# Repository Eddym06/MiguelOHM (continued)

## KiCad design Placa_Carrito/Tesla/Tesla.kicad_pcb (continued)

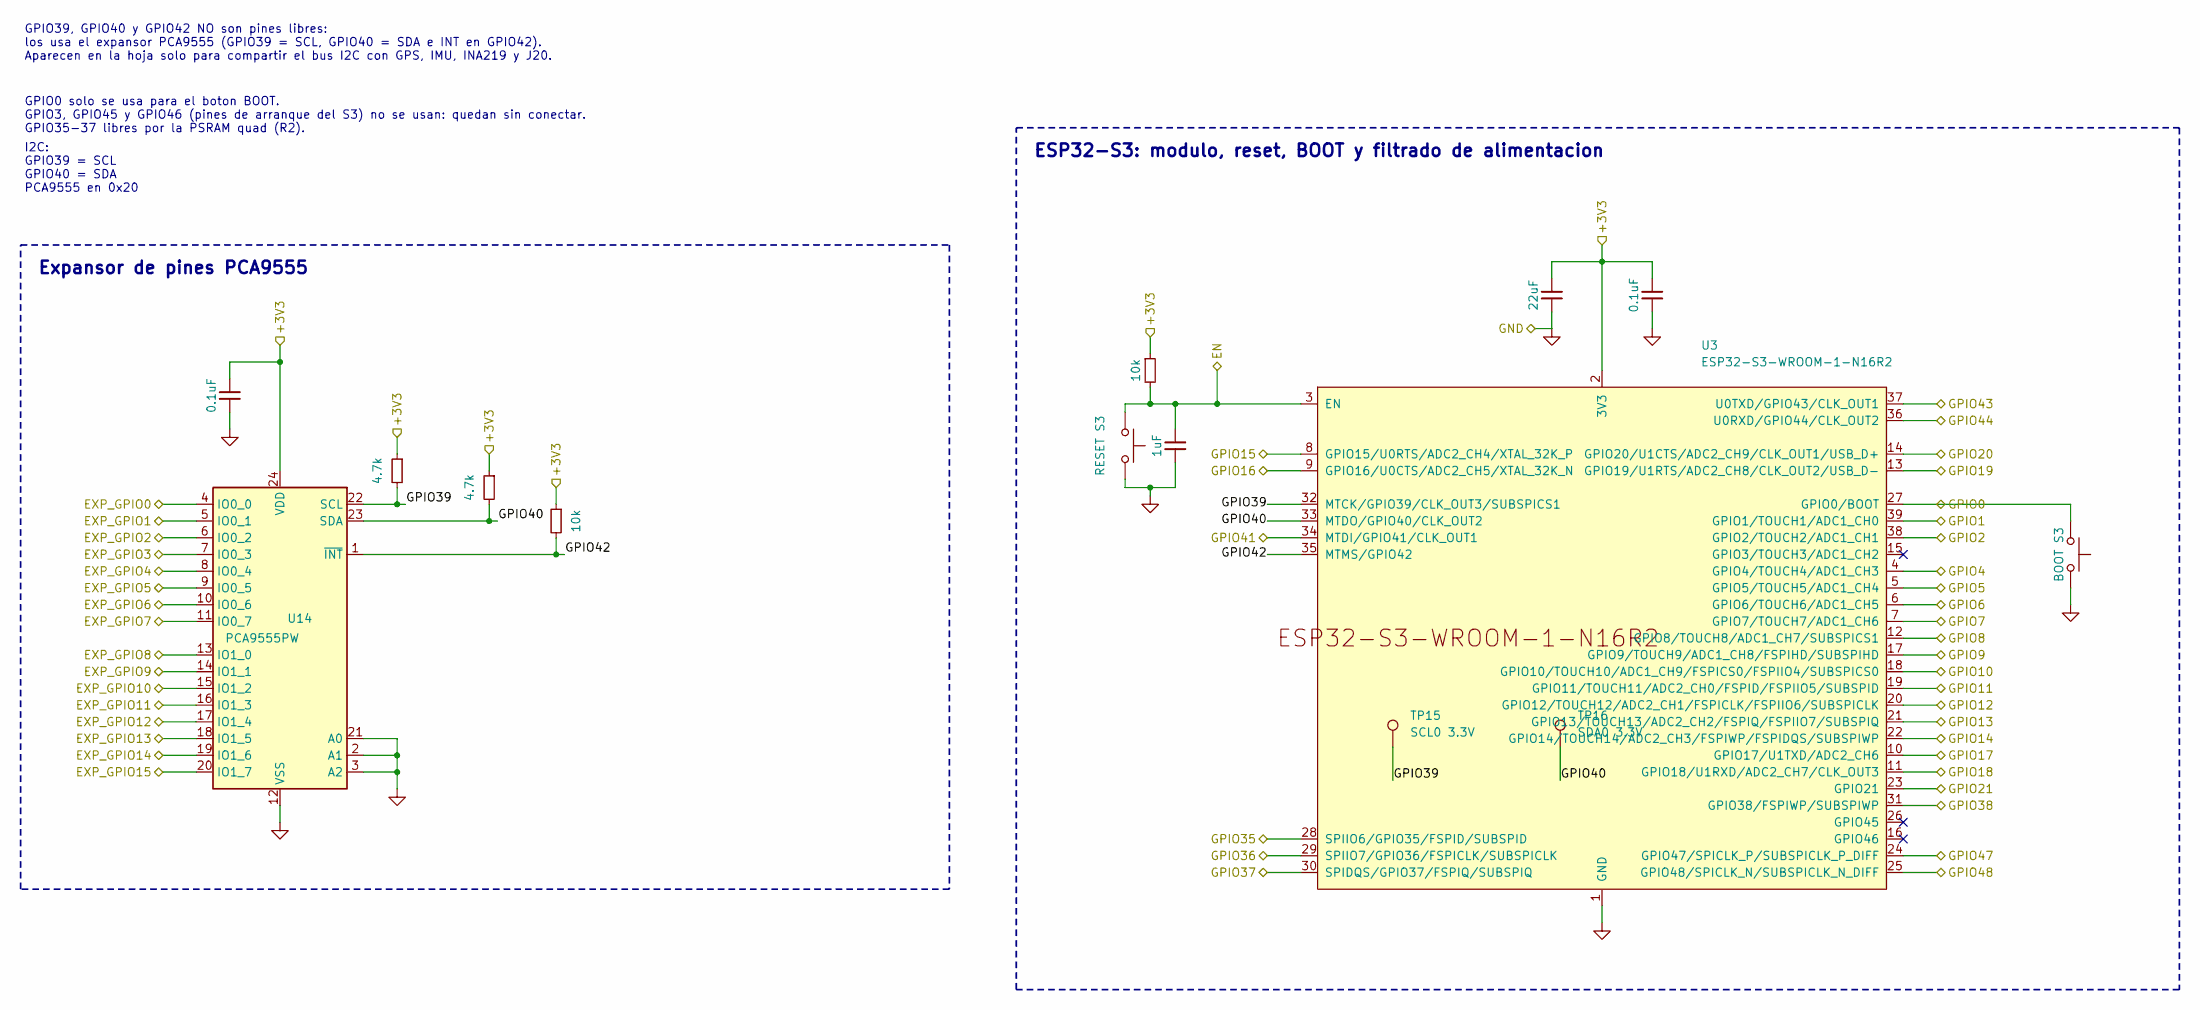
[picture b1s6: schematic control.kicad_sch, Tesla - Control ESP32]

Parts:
C131: 22uF; C_0805_2012Metric; LCSC C45783
C132, C138: 0.1uF; C_0402_1005Metric; LCSC C307331
C133: 1uF; C_0402_1005Metric; LCSC C52923
R21, R22: 4.7k; R_0402_1005Metric; LCSC C25900
R52, R63: 10k; R_0402_1005Metric; LCSC C25744
SW1: BOOT S3; SW_Push_1P1T_XKB_TS-1187A; LCSC C318884
SW4: RESET S3; SW_Push_1P1T_XKB_TS-1187A; LCSC C318884
TP15: SCL0 3.3V; TestPoint_Pad_D1.5mm
TP16: SDA0 3.3V; TestPoint_Pad_D1.5mm
U3: ESP32-S3-WROOM-1-N16R2; ESP32-S3-WROOM-1; LCSC C2913205
U14: PCA9555PW; TSSOP-24_4.4x7.8mm_P0.65mm; LCSC C128392

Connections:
+3V3: C131.1, C132.1, C138.1, R21.1, R22.1, R52.1, R63.1, U3.2 (3V3), U14.24 (VDD); also elsewhere on the board
/ENC_A1: U3.8 (GPIO15/U0RTS/ADC2_CH4/XTAL_32K_P); also elsewhere on the board
/ENC_A2: U3.9 (GPIO16/U0CTS/ADC2_CH5/XTAL_32K_N); also elsewhere on the board
/ENC_B1: U3.21 (GPIO13/TOUCH13/ADC2_CH2/FSPIQ/FSPIIO7/S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); also elsewhere on the board
/ENC_B2: U3.22 (GPIO14/TOUCH14/ADC2_CH3/FSPIWP/FSPIDQS/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); also elsewhere on the board
/Externo/Control ESP32/GPIO39: R21.2, TP15.1, U3.32 (MTCK/GPIO39/CLK_OUT3/SUBSPICS1), U14.22 (SCL)
/Externo/Control ESP32/GPIO40: R22.2, TP16.1, U3.33 (MTDO/GPIO40/CLK_OUT2), U14.23 (SDA)
/Externo/Control ESP32/GPIO42: R63.2, U3.35 (MTMS/GPIO42), U14.1 (~INT)
/Externo/EN: C133.1, R52.2, SW4.1, U3.3 (EN); also elsewhere on the board
/Externo/EXP_GPIO1: U14.5 (IO0_1); also elsewhere on the board
/Externo/EXP_GPIO2: U14.6 (IO0_2); also elsewhere on the board
/Externo/EXP_GPIO3: U14.7 (IO0_3); also elsewhere on the board
/Externo/EXP_GPIO8: U14.13 (IO1_0); also elsewhere on the board
/Externo/EXP_GPIO9: U14.14 (IO1_1); also elsewhere on the board
/Externo/EXP_GPIO10: U14.15 (IO1_2); also elsewhere on the board
/Externo/EXP_GPIO11: U14.16 (IO1_3); also elsewhere on the board
/Externo/EXP_GPIO12: U14.17 (IO1_4); also elsewhere on the board
/Externo/EXP_GPIO13: U14.18 (IO1_5); also elsewhere on the board
/Externo/EXP_GPIO14: U14.19 (IO1_6); also elsewhere on the board
/Externo/EXP_GPIO15: U14.20 (IO1_7); also elsewhere on the board
/Externo/GPIO0: SW1.1, U3.27 (GPIO0/BOOT); also elsewhere on the board
/Externo/GPIO1: U3.39 (GPIO1/TOUCH1/ADC1_CH0); also elsewhere on the board
/Externo/GPIO2: U3.38 (GPIO2/TOUCH2/ADC1_CH1); also elsewhere on the board
/Externo/GPIO4: U3.4 (GPIO4/TOUCH4/ADC1_CH3); also elsewhere on the board
/Externo/GPIO5: U3.5 (GPIO5/TOUCH5/ADC1_CH4); also elsewhere on the board
/Externo/GPIO6: U3.6 (GPIO6/TOUCH6/ADC1_CH5); also elsewhere on the board
/Externo/GPIO7: U3.7 (GPIO7/TOUCH7/ADC1_CH6); also elsewhere on the board
/Externo/GPIO8: U3.12 (GPIO8/TOUCH8/ADC1_CH7/SUBSPICS1); also elsewhere on the board
/Externo/GPIO9: U3.17 (GPIO9/TOUCH9/ADC1_CH8/FSPIHD/SUBSPIHD); also elsewhere on the board
/Externo/GPIO10: U3.18 (GPIO10/TOUCH10/ADC1_CH9/FSPICS0/FSPIIO4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); also elsewhere on the board
/Externo/GPIO11: U3.19 (GPIO11/TOUCH11/ADC2_CH0/FSPID/FSPIIO5/S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); also elsewhere on the board
/Externo/GPIO37: U3.30 (SPIDQS/GPIO37/FSPIQ/SUBSPIQ); also elsewhere on the board
/Externo/GPIO38: U3.31 (GPIO38/FSPIWP/SUBSPIWP); also elsewhere on the board
/Externo/GPIO41: U3.34 (MTDI/GPIO41/CLK_OUT1); also elsewhere on the board
/Externo/GPIO43: U3.37 (U0TXD/GPIO43/CLK_OUT1); also elsewhere on the board
/Externo/GPIO44: U3.36 (U0RXD/GPIO44/CLK_OUT2); also elsewhere on the board
/GPS_RX: U3.24 (GPIO47/SPICLK_P/SUBSPICLK_P_DIFF); also elsewhere on the board
/GPS_SCL: U3.10 (GPIO17/U1TXD/ADC2_CH6); also elsewhere on the board
/GPS_SDA: U3.11 (GPIO18/U1RXD/ADC2_CH7/CLK_OUT3); also elsewhere on the board
/GPS_TX: U3.25 (GPIO48/SPICLK_N/SUBSPICLK_N_DIFF); also elsewhere on the board
/LED_A_ADELANTE: U14.8 (IO0_4); also elsewhere on the board
/LED_A_ATRAS: U14.9 (IO0_5); also elsewhere on the board
/LED_B_ADELANTE: U14.10 (IO0_6); also elsewhere on the board
/LED_B_ATRAS: U14.11 (IO0_7); also elsewhere on the board
/LIDAR_PWM: U14.4 (IO0_0); also elsewhere on the board
/LIDAR_RX: U3.29 (SPIIO7/GPIO36/FSPICLK/SUBSPICLK); also elsewhere on the board
/SERVO_1: U3.23 (GPIO21); also elsewhere on the board
/SERVO_2: U3.28 (SPIIO6/GPIO35/FSPID/SUBSPID); also elsewhere on the board
/SERVO_DIR: U3.20 (GPIO12/TOUCH12/ADC2_CH1/FSPICLK/FSPIIO6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); also elsewhere on the board
/USB JTAG (USB nativo del S3)/USB_S3_DM: U3.13 (GPIO19/U1RTS/ADC2_CH8/CLK_OUT2/USB_D-); also elsewhere on the board
/USB JTAG (USB nativo del S3)/USB_S3_DP: U3.14 (GPIO20/U1CTS/ADC2_CH9/CLK_OUT1/USB_D+); also elsewhere on the board
GND: C131.2, C132.2, C133.2, C138.2, SW1.2, SW4.2, U3.1 (GND), U3.40 (GND), U3.41 (GND), U14.2 (A1), U14.3 (A2), U14.12 (VSS), U14.21 (A0); also elsewhere on the board

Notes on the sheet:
GPIO0 solo se usa para el boton BOOT. GPIO3, GPIO45 y GPIO46 (pines de arranque del S3) no se usan: quedan sin conectar. GPIO35-37 libres por la PSRAM quad (R2).
Expansor de pines PCA9555
I2C: GPIO39 = SCL GPIO40 = SDA PCA9555 en 0x20
GPIO39, GPIO40 y GPIO42 NO son pines libres: los usa el expansor PCA9555 (GPIO39 = SCL, GPIO40 = SDA e INT en GPIO42). Aparecen en la hoja solo para compartir el bus I2C con GPS, IMU, INA219 y J20.
ESP32-S3: modulo, reset, BOOT y filtrado de alimentacion

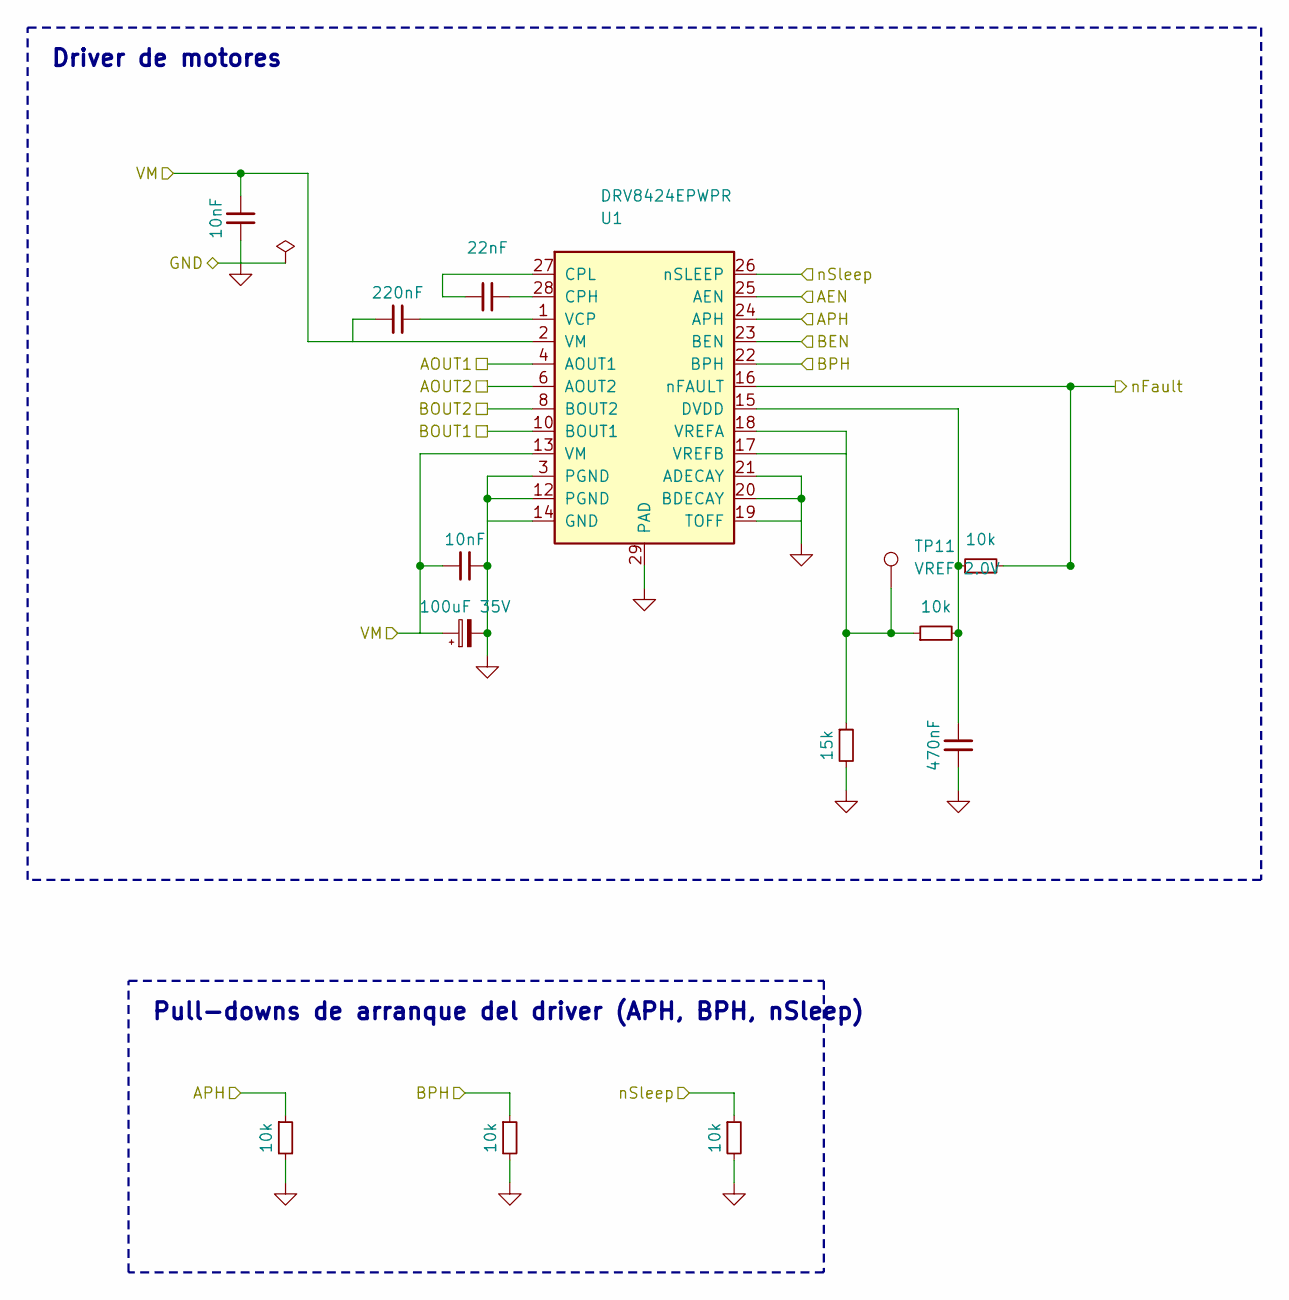
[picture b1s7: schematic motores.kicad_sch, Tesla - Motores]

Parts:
C1: 22nF; C_0805_2012Metric; LCSC C1729
C2: 220nF; C_0805_2012Metric; LCSC C5378
C3, C4: 10nF; C_0805_2012Metric; LCSC C1710
C5: 470nF; C_0805_2012Metric; LCSC C13967
C6: 100uF 35V; CP_Elec_6.3x7.7; LCSC C350012
R2, R3, R64, R65, R66: 10k; R_0402_1005Metric; LCSC C25744
R4: 15k; R_0402_1005Metric; LCSC C25756
TP11: VREF 2.0V; TestPoint_Pad_D1.5mm
U1: DRV8424EPWPR; SOP65P640X120-29N; LCSC C2862906

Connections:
/Externo/AOUT1: U1.4 (AOUT1), U1.5 (AOUT1); also elsewhere on the board
/Externo/AOUT2: U1.6 (AOUT2), U1.7 (AOUT2); also elsewhere on the board
/Externo/BOUT1: U1.10 (BOUT1), U1.11 (BOUT1); also elsewhere on the board
/Externo/BOUT2: U1.8 (BOUT2), U1.9 (BOUT2); also elsewhere on the board
/Externo/GPIO1: U1.25 (AEN); also elsewhere on the board
/Externo/GPIO2: R64.1, U1.24 (APH); also elsewhere on the board
/Externo/GPIO4: U1.23 (BEN); also elsewhere on the board
/Externo/GPIO5: R65.1, U1.22 (BPH); also elsewhere on the board
/Externo/GPIO6: R66.1, U1.26 (nSLEEP); also elsewhere on the board
/Externo/GPIO7: R2.2, U1.16 (nFAULT); also elsewhere on the board
/Externo/VBAT: C2.2, C3.2, C4.2, C6.1, U1.2 (VM), U1.13 (VM); also elsewhere on the board
GND: C3.1, C4.1, C5.1, C6.2, R4.2, R64.2, R65.2, R66.2, U1.3 (PGND), U1.12 (PGND), U1.14 (GND), U1.19 (TOFF), U1.20 (BDECAY), U1.21 (ADECAY), U1.29 (PAD); also elsewhere on the board
unnamed: C1.1, U1.28 (CPH)
unnamed: C1.2, U1.27 (CPL)
unnamed: C5.2, R2.1, R3.2, U1.15 (DVDD)
unnamed: C2.1, U1.1 (VCP)
unnamed: R3.1, R4.1, TP11.1, U1.17 (VREFB), U1.18 (VREFA)

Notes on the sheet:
Pull-downs de arranque del driver (APH, BPH, nSleep)
Driver de motores

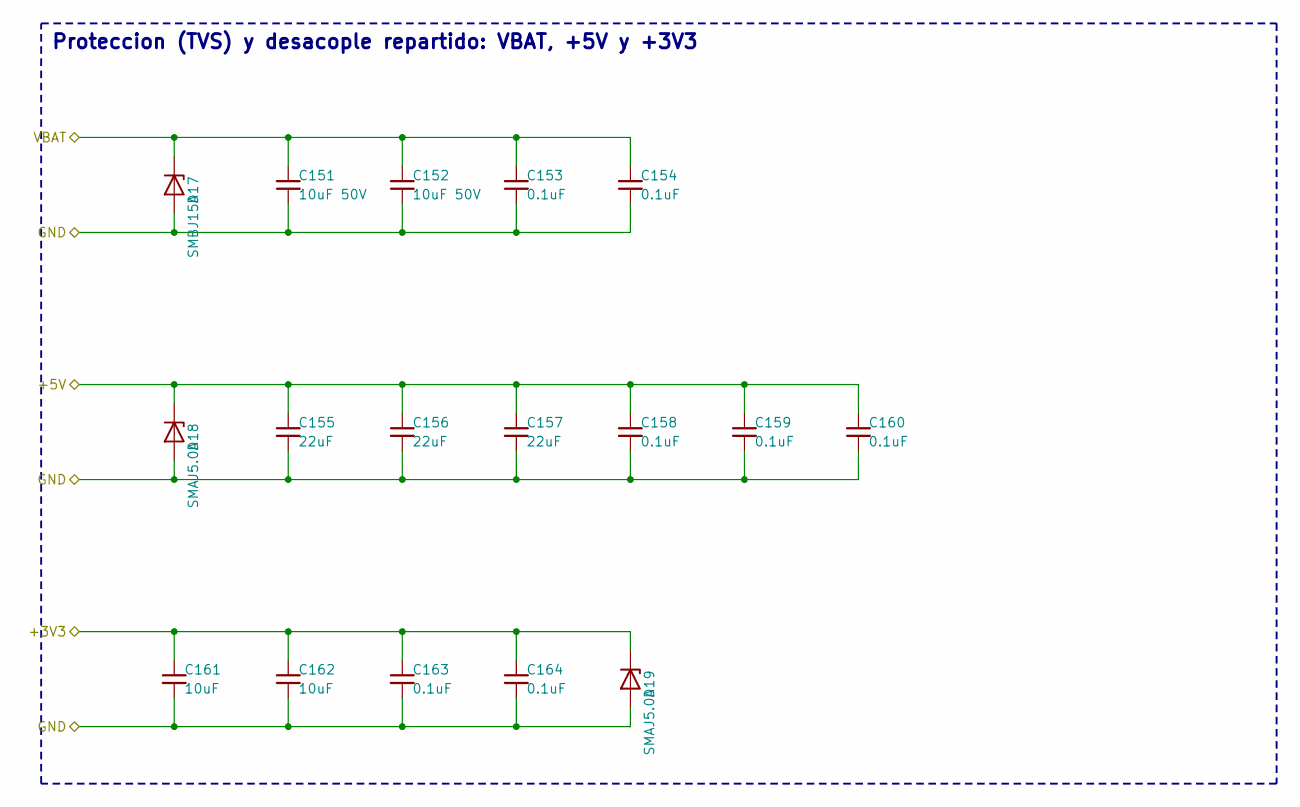
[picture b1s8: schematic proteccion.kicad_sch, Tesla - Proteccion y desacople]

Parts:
C151, C152: 10uF 50V; C_0805_2012Metric; LCSC C440198
C153, C154, C158, C159, C160, C163, C164: 0.1uF; C_0402_1005Metric; LCSC C307331
C155, C156, C157: 22uF; C_0805_2012Metric; LCSC C45783
C161, C162: 10uF; C_0805_2012Metric; LCSC C15850
D17: SMBJ15A; D_SMB; LCSC C83846
D18, D19: SMAJ5.0A; D_SMA; LCSC C83329

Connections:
+3V3: C161.1, C162.1, C163.1, C164.1, D19.1 (K); also elsewhere on the board
+5V: C155.1, C156.1, C157.1, C158.1, C159.1, C160.1, D18.1 (K); also elsewhere on the board
/Externo/VBAT: C151.1, C152.1, C153.1, C154.1, D17.1 (K); also elsewhere on the board
GND: C151.2, C152.2, C153.2, C154.2, C155.2, C156.2, C157.2, C158.2, C159.2, C160.2, C161.2, C162.2, C163.2, C164.2, D17.2 (A), D18.2 (A), D19.2 (A); also elsewhere on the board

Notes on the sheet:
Proteccion (TVS) y desacople repartido: VBAT, +5V y +3V3

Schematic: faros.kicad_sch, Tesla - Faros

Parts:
C88, C141, C142: 10uF 50V; C_0805_2012Metric; LCSC C440198
C89, C94, C143, C144: 0.1uF; C_0402_1005Metric; LCSC C307331
C95: 470uF; CP_Elec_6.3x7.7; LCSC C2858856
D7, D11, D12: SS14; D_SMA; LCSC C2480
L7, L8, L9: 100uH; L_Sunlord_SWPA6045S; LCSC C60633
R25, R70, R71: 0.3; R_0805_2012Metric; LCSC C705492
R26, R72, R73: 10k; R_0402_1005Metric; LCSC C25744
R30: 330; R_0402_1005Metric; LCSC C25104
U9, U15, U16: AL8861WT-7; TSOT-23-5; LCSC C581338
U10: 74AHCT1G125W5-7; SOT-23-5; LCSC C842287

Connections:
+5V: C94.1, C95.1, U10.5 (VCC); also elsewhere on the board
/Externo/FAROS_NEG: L7.2; also elsewhere on the board
/Externo/FAROS_POS: R25.2, U9.4 (SET); also elsewhere on the board
/Externo/GPIO8: U10.2; also elsewhere on the board
/Externo/GPIO9: R73.1, U16.3 (CTRL); also elsewhere on the board
/Externo/GPIO10: R72.1, U15.3 (CTRL); also elsewhere on the board
/Externo/GPIO11: R26.1, U9.3 (CTRL); also elsewhere on the board
/Externo/INT_DER_NEG: L9.2; also elsewhere on the board
/Externo/INT_DER_POS: R71.2, U16.4 (SET); also elsewhere on the board
/Externo/INT_IZQ_NEG: L8.2; also elsewhere on the board
/Externo/INT_IZQ_POS: R70.2, U15.4 (SET); also elsewhere on the board
/Externo/TIRA_LED_5V: R30.2; also elsewhere on the board
/Externo/VBAT: C88.1, C89.1, C141.1, C142.1, C143.1, C144.1, D7.1 (K), D11.1 (K), D12.1 (K), R25.1, R70.1, R71.1, U9.5 (VIN), U15.5 (VIN), U16.5 (VIN); also elsewhere on the board
GND: C88.2, C89.2, C94.2, C95.2, C141.2, C142.2, C143.2, C144.2, R26.2, R72.2, R73.2, U9.2 (GND), U10.1, U10.3 (GND), U15.2 (GND), U16.2 (GND); also elsewhere on the board
unnamed: D7.2 (A), L7.1, U9.1 (SW)
unnamed: D11.2 (A), L8.1, U15.1 (SW)
unnamed: D12.2 (A), L9.1, U16.1 (SW)
unnamed: R30.1, U10.4

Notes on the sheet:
Faros (driver de LED)
Tira LED (adaptador 3,3 V a 5 V)
Intermitente derecho (driver de LED)
Intermitente izquierdo (driver de LED)

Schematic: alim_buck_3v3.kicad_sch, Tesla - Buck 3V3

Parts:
C45: 10uF 50V; C_0805_2012Metric; LCSC C440198
C46: 0.1uF; C_0402_1005Metric; LCSC C307331
C47, C48: 22uF; C_0805_2012Metric; LCSC C45783
C146: 100pF; C_0402_1005Metric; LCSC C1546
L4: 6.8uH; L_Changjiang_FXL0530; LCSC C177249
R79: 191k; R_0402_1005Metric; LCSC C159084
R80: 62k; R_0402_1005Metric; LCSC C37825
U6: AP63200WU-7; TSOT-23-6; LCSC C2071868

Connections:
+3V3: C47.1, C48.1, C146.2, L4.2, R79.2; also elsewhere on the board
/Externo/VBAT: C45.1, U6.2 (EN), U6.3 (IN); also elsewhere on the board
GND: C45.2, C47.2, C48.2, R80.2, U6.4 (GND); also elsewhere on the board
unnamed: C46.1, U6.6 (BST)
unnamed: C146.1, R79.1, R80.1, U6.1 (FB)
unnamed: C46.2, L4.1, U6.5 (SW)

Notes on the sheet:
Buck 3,3 V (VM a +3V3)

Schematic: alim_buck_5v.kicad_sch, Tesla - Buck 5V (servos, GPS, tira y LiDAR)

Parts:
C69: 10uF 50V; C_0805_2012Metric; LCSC C440198
C70: 0.1uF; C_0402_1005Metric; LCSC C307331
C71, C72, C75: 22uF; C_0805_2012Metric; LCSC C45783
C77: 470uF; CP_Elec_6.3x7.7; LCSC C2858856
C139: 2.7nF; C_0402_1005Metric; LCSC C106251
L5: 3.3uH; L_Changjiang_FXL0650; LCSC C485362
R67: 115k; R_0402_1005Metric; LCSC C25747
R68: 22.1k; R_0402_1005Metric; LCSC C43473
R69: 15.8k; R_0402_1005Metric; LCSC C26956
R78: 200k; R_0402_1005Metric; LCSC C25764
U7: AP64500SP-13; SOIC-8-1EP_3.9x4.9mm_P1.27mm_EP2.41x3.3mm; LCSC C2070920

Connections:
+5V: C71.1, C72.1, C75.1, C77.1, L5.2, R67.1; also elsewhere on the board
/Externo/VBAT: C69.1, U7.2 (VIN), U7.3 (EN); also elsewhere on the board
GND: C69.2, C71.2, C72.2, C75.2, C77.2, C139.2, R68.2, R78.2, U7.7 (GND), U7.9 (EP); also elsewhere on the board
unnamed: C139.1, R69.2
unnamed: C70.1, U7.1 (BST)
unnamed: R69.1, U7.6 (COMP)
unnamed: R67.2, R68.1, U7.5 (FB)
unnamed: R78.1, U7.4 (RT/CLK)
unnamed: C70.2, L5.1, U7.8 (SW)

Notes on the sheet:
Buck 5 V (VCC a +5V), AP64501: 5 A

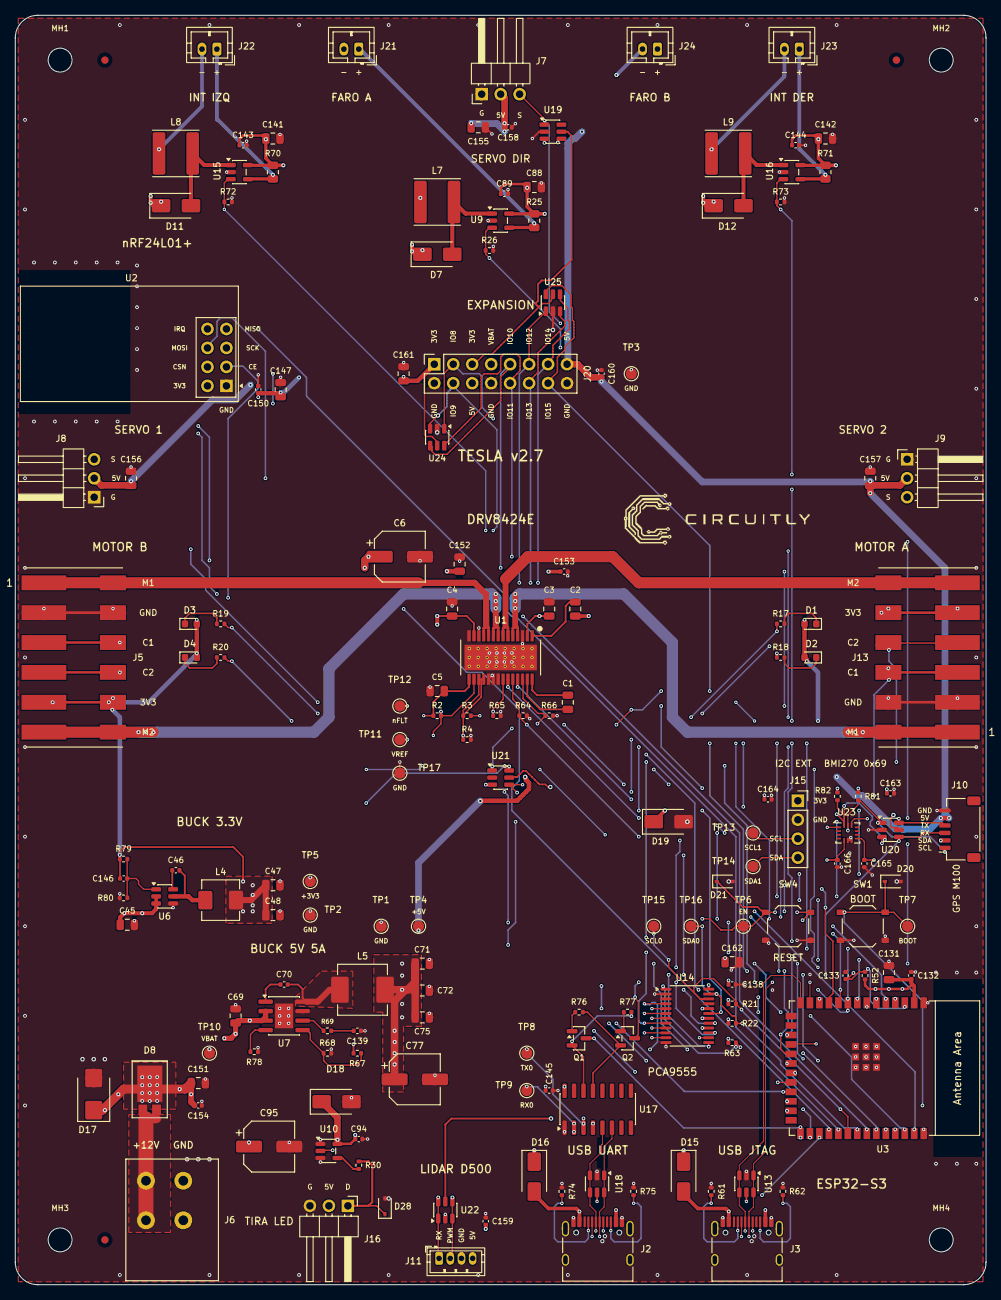
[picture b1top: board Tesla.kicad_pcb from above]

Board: 6 copper layers, 130.0 x 170.0 mm, 170 parts (0 on the bottom side), 101 nets.

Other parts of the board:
FID1, FID2, FID3: Fiducial; Fiducial_1mm_Mask2mm

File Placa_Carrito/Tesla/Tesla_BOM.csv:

Referencias,Cant,Valor,Huella,LCSC,Tipo JLCPCB,Existencias,USD c/u,Notas
C1,1,22nF,Capacitor_SMD:C_0805_2012Metric,C107147,Extendida,361532,0.0061,YAGEO CC0805KRX7R9BB223 X7R 50V
C2,1,220nF,Capacitor_SMD:C_0805_2012Metric,C107131,Extendida,192839,0.0138,YAGEO CC0805KKX7R9BB224 X7R 50V
"C3,C4",2,10nF,Capacitor_SMD:C_0805_2012Metric,C83170,Extendida,1030359,0.0065,YAGEO CC0805KRX7R9BB103 X7R 50V
C5,1,470nF,Capacitor_SMD:C_0805_2012Metric,C106846,Extendida,17919,0.019,YAGEO CC0805KKX7R8BB474 X7R 25V
C6,1,100uF,Capacitor_SMD:CP_Elec_6.3x7.7,C2836443,Extendida,52501,0.0395,KNSCHA RVT100UF25V67RV0011 electrolitico SMD 25V 6.3x7.7
"C45,C69,C88,C141,C142,C161,C162",7,10uF,Capacitor_SMD:C_0805_2012Metric,C5448891,Extendida,215730,0.0233,CCTC TCC0805X5R106K250FT X5R 25V
"C46,C70,C89,C94,C132,C138,C143,C144,C145,C150,C158,C159,C160,C163,C164",15,0.1uF,Capacitor_SMD:C_0402_1005Metric,C60474,Extendida,5212697,0.0038,YAGEO CC0402KRX7R7BB104 X7R 16V
"C47,C48,C71,C72,C75,C131,C147,C151,C152,C155,C156,C157",12,22uF,Capacitor_SMD:C_0805_2012Metric,C6119899,Extendida,784709,0.078,HRE CGA0805X5R226M250MT X5R 25V (menos perdida por sesgo DC)
"C77,C95",2,470uF,Capacitor_SMD:CP_Elec_6.3x7.7,C2858856,Extendida,132709,0.0457,KNSCHA RVT470UF10V67RV0159 electrolitico SMD 10V 6.3x7.7
C133,1,1uF,Capacitor_SMD:C_0402_1005Metric,C325464,Extendida,543814,0.0109,YAGEO CC0402KRX5R7BB105 X5R 16V
C139,1,2.7nF,Capacitor_SMD:C_0402_1005Metric,C106251,Extendida,90031,0.0066,YAGEO CC0402KRX7R9BB272 X7R 50V
C146,1,100pF,Capacitor_SMD:C_0402_1005Metric,C1546,Basic,2570014,0.0018,FH 0402CG101J500NT C0G 50V
"C153,C154",2,0.1uF,Capacitor_SMD:C_0402_1005Metric,C131394,Extendida,9108350,0.0106,100nF 50V (desacople VBAT)
"D1,D3",2,KT-0603G,LED_SMD:LED_0603_1608Metric,C12624,Extendida,151134,0.0119,Hubei KENTO KT-0603G LED verde 0603
"D2,D4",2,KT-0603R,LED_SMD:LED_0603_1608Metric,C2286,Basic,8533910,0.0077,Hubei KENTO KT-0603R LED rojo 0603
"D7,D11,D12,D15,D16",5,SS14,Diode_SMD:D_SMA,C2480,Basic,1046438,0.0192,MDD SS14 Schottky 40V 1A SMA
D8,1,SS10U45,Tesla_Parts:TO-277_SS10U45,C698773,Extendida,17026,0.2629,Yangjie SS10U45 Schottky 45V 10A TO-277
D17,1,SMBJ15A,Diode_SMD:D_SMB,C83846,Extendida,28362,0.1341,TVS SMBJ15A 15V 600W (VBAT)
D18,1,SMAJ5.0A,Diode_SMD:D_SMA,C83329,Extendida,41338,0.1112,TVS SMAJ5.0A 5V 400W (+5V)
"J2,J3",2,USB-C,Connector_USB:USB_C_Receptacle_HRO_TYPE-C-31-M-12,C165948,Extendida,404656,0.1869,HRO TYPE-C-31-M-12 USB-C 16P
"J5,J13",4,Motor JGB37-520 (2x WAGO 2060-453),Tesla_Parts:WAGO_2060-453_x2_6P_SMD,C2765056,Extendida,2668,0.6236,WAGO 2060-453/998-404 borne de resorte SMD 3 polos (2 por motor)
J6,1,Bateria 12V (WAGO 2604-1102),Tesla_Parts:WAGO_2604-1102_2P_THT,C3309286,Extendida,347,3.1832,"WAGO 2604-1102 borne de resorte 2 polos 20 A, cable de 0,2 a 4 mm2 (12-24 AWG), entrada horizontal"
J10,1,GPS M100 Pro (JST SH 6),Connector_JST:JST_SH_SM06B-SRSS-TB_1x06-1MP_P1.00mm_Horizontal,C160405,Extendida,15909,0.8969,JST SM06B-SRSS-TB(LF)(SN)
J11,1,LiDAR D500 (ZH 1.5),Connector_JST:JST_ZH_B4B-ZR_1x04_P1.50mm_Vertical,C157997,Extendida,20355,0.104,JST B4B-ZR(LF)(SN)
J15,1,IMU I2C (GY-521),Connector_PinSocket_2.54mm:PinSocket_1x04_P2.54mm_Vertical,C2718488,Extendida,143964,0.0807,BOOMELE 2.54-1*4PFemale socket 1x4
J16,1,Tira WS2812,Connector_PinHeader_2.54mm:PinHeader_1x03_P2.54mm_Horizontal,C492411,Extendida,86838,0.0254,XFCN PZ254R-11-03P header 1x3 angulo recto
J20,1,Expansion S3 + PCA9555,Connector_PinSocket_2.54mm:PinSocket_2x08_P2.54mm_Vertical,C30734,Extendida,38738,0.155,BOOMELE 2.54-2*8PFemale socket hembra 2x8
J24,1,Faro delantero 2,Connector_JST:JST_PH_B2B-PH-K_1x02_P2.00mm_Vertical,C131337,Extendida,331296,0.0328,JST B2B-PH-K-S(LF)(SN)
L4,1,6.8uH,Inductor_SMD:L_Changjiang_FXL0530,C177249,Extendida,82115,0.1424,cjiang FXL0530-6R8-M 6.8uH Isat 4A DCR 90mR
L5,1,3.3uH,Inductor_SMD:L_Changjiang_FXL0650,C485362,Extendida,1824,0.186,cjiang FXL0650-3R3-M 3.3uH Isat 10A DCR 22mR
"L7,L8,L9",3,100uH,Inductor_SMD:L_Sunlord_SWPA6045S,C60633,Extendida,4991,0.0938,Sunlord SWPA6045S101MT 100uH
"Q1,Q2",2,MMBT3904,Package_TO_SOT_SMD:SOT-23,C20526,Basic,3989908,0.0103,Changjiang MMBT3904 NPN SOT-23
"R1,R3",2,15k,Resistor_SMD:R_0402_1005Metric,C25756,Basic,1869965,0.0011,UNI-ROYAL 0402WGF1502TCE 1%
"R2,R4,R26,R52,R63,R64,R65,R66,R72,R73,R76,R77",12,10k,Resistor_SMD:R_0402_1005Metric,C25744,Basic,32141343,0.0009,UNI-ROYAL 0402WGF1002TCE 1%
"R17,R18,R19,R20,R30",5,330,Resistor_SMD:R_0402_1005Metric,C25104,Basic,1970628,0.0011,"UNI-ROYAL 0402WGF3300TCE 1% (LED a 3,3 V)"
"R21,R22",2,4.7k,Resistor_SMD:R_0402_1005Metric,C25900,Basic,12032462,0.0016,UNI-ROYAL 0402WGF4701TCE 1%
"R25,R70,R71",3,0.3,Resistor_SMD:R_0805_2012Metric,C705492,Extendida,13167,0.0119,YAGEO RL0805FR-070R3L 0.3R 1%
"R61,R62,R74,R75",4,5.1k,Resistor_SMD:R_0402_1005Metric,C25905,Basic,5239852,0.0014,UNI-ROYAL 0402WGF5101TCE 1%
R67,1,115k,Resistor_SMD:R_0402_1005Metric,C25747,Extendida,64859,0.0014,UNI-ROYAL 0402WGF1153TCE 1%
R68,1,22.1k,Resistor_SMD:R_0402_1005Metric,C43473,Extendida,45546,0.0011,UNI-ROYAL 0402WGF2212TCE 1%
R69,1,15.8k,Resistor_SMD:R_0402_1005Metric,C26956,Extendida,157757,0.0012,UNI-ROYAL 0402WGF1582TCE 1%
R78,1,200k,Resistor_SMD:R_0402_1005Metric,C25764,Basic,3139322,0.0013,UNI-ROYAL 0402WGF2003TCE 1% (RT del AP64500: 500 kHz)
R79,1,196k,Resistor_SMD:R_0402_1005Metric,C26996,Extendida,6667,0.0023,UNI-ROYAL 0402WGF1963TCE 1%
R80,1,62k,Resistor_SMD:R_0402_1005Metric,C37825,Extendida,373641,0.0011,UNI-ROYAL 0402WGF6202TCE 1%
SW4,1,RESET S3,Button_Switch_SMD:SW_Push_1P1T_XKB_TS-1187A,C318884,Basic,652548,0.0197,XKB TS-1187A-B-A-B pulsador SMD 5.1x5.1
U1,1,DRV8424EPWPR,Tesla_Parts:SOP65P640X120-29N,C2862906,Extendida,241,4.2224,TI DRV8424EPWPR HTSSOP-28 PowerPAD
U2,1,nRF24L01+ (modulo en socket 2x4),RF_Module:nRF24L01_Breakout,C239344,Extendida,10730,0.1754,CJT A2541HWV-2x4P socket hembra 2x4 para el modulo
U3,1,ESP32-S3-WROOM-1-N16R2,Espressif_S3:ESP32-S3-WROOM-1,C2913205,Extendida,6514,5.1061,Espressif ESP32-S3-WROOM-1-N16R2
U6,1,AP63200WU-7,Package_TO_SOT_SMD:TSOT-23-6,C2071868,Extendida,5202,1.1702,Diodes AP63200WU-7 buck 2A ajustable
U7,1,AP64500SP-13,Package_SO:SOIC-8-1EP_3.9x4.9mm_P1.27mm_EP2.41x3.3mm,C2070920,Extendida,5553,1.4451,Diodes AP64500SP-13 buck sincrono 5A
"U9,U15,U16",3,AL8861WT-7,Package_TO_SOT_SMD:TSOT-23-5,C581338,Extendida,15530,0.9378,Diodes AL8861WT-7 driver LED 1A (mismo pinout que AL8860)
U10,1,74AHCT1G125W5-7,Package_TO_SOT_SMD:SOT-23-5,C842287,Extendida,789,0.1226,Diodes 74AHCT1G125W5-7 SOT-25
"U13,U18,U22",3,USBLC6-2SC6,Package_TO_SOT_SMD:SOT-23-6,C7519,Extendida,33049,0.1521,ST USBLC6-2SC6
U14,1,PCA9555PW,Package_SO:TSSOP-24_4.4x7.8mm_P0.65mm,C128392,Extendida,57322,1.2406,"NXP PCA9555PW,118"
U17,1,CH340C,Package_SO:SOIC-16_3.9x9.9mm_P1.27mm,C7464026,Extendida,619,0.5974,WCH CH340C SOP-16
"U19,U20,U21",3,SRV05-4HTG-D,Package_TO_SOT_SMD:SOT-23-6,C1975211,Extendida,35794,0.1616,ESD 4 canales SRV05-4

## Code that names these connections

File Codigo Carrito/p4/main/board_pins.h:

#pragma once
// =====================================================================================
//  PINES DEL ESP32-P4 DEL CARRITO  -  PENDIENTES DE LA PCB
//  Todo en PIN_NC (-1) hasta que se defina la PCB. Un modulo con algun pin en -1 se
//  desactiva y el firmware lo avisa en el log al arrancar; nada se bloquea.
// =====================================================================================

#define PIN_NC   (-1)
// mascara de bit de un pin (seguro aunque el pin sea -1 en tiempo de compilacion)
#define PIN_BIT(p)  (1ULL << ((p) < 0 ? 0 : (p)))

// ---- Radio 433 MHz (UART) ----
#define PIN_RF_TX        PIN_NC   // DAT del transmisor
#define PIN_RF_RX        PIN_NC   // DO del receptor
#define PIN_RF_EN        PIN_NC   // EN del transmisor
#define RF_EN_ACTIVE_HIGH 1
#define RF_UART_NUM      1

// ---- Puente H L298N (motor izquierdo = A, derecho = B) ----
#define PIN_MOT_L_EN     PIN_NC   // ENA (PWM 5 kHz)
#define PIN_MOT_L_IN1    PIN_NC
#define PIN_MOT_L_IN2    PIN_NC
#define PIN_MOT_R_EN     PIN_NC   // ENB (PWM 5 kHz)
#define PIN_MOT_R_IN1    PIN_NC   // IN3
#define PIN_MOT_R_IN2    PIN_NC   // IN4
#define MOTOR_PWM_HZ     5000

// ---- Encoders en cuadratura (canal A y B de cada motor) ----
#define PIN_ENC_L_A      PIN_NC
#define PIN_ENC_L_B      PIN_NC
#define PIN_ENC_R_A      PIN_NC
#define PIN_ENC_R_B      PIN_NC

// ---- Servo de direccion (MG90) ----
#define PIN_SERVO        PIN_NC

// ---- Luces ----
#define PIN_HEADLIGHTS   PIN_NC   // base del transistor NPN de los faros
#define PIN_RGB_R        PIN_NC   // LEDs RGB de las ruedas (4 en paralelo, comunes)
#define PIN_RGB_G        PIN_NC
#define PIN_RGB_B        PIN_NC
#define RGB_COMMON_ANODE 0        // 1 si el driver invierte la logica
#define PIN_SPOILER      PIN_NC   // DIN de la tira WS2812 del aleron

// ---- Bus I2C: BMI160, INA219, brujula del GPS ----
#define PIN_I2C_SDA      PIN_NC
#define PIN_I2C_SCL      PIN_NC
#define BMI160_ADDR      0x68     // 0x69 si SDO esta a 3V3
#define INA219_ADDR      0x40
#define INA219_SHUNT_MOHM 100     // resistencia shunt del modulo (R100 = 100 mohm)

// ---- GPS M100 Pro (UART, NMEA) ----
#define PIN_GPS_RX       PIN_NC   // RX del P4 <- TX del GPS
#define PIN_GPS_TX       PIN_NC   // TX del P4 -> RX del GPS (opcional)
#define GPS_UART_NUM     2

// ---- LIDAR D6 (UART 230400, solo se recibe) ----
#define PIN_LIDAR_RX     PIN_NC
#define LIDAR_UART_NUM   3
#define LIDAR_BAUD       230400

// ---- Enlace SPI con el ESP32-S3 (el P4 es maestro) ----
#define PIN_SPI_SCLK     PIN_NC
#define PIN_SPI_MOSI     PIN_NC
#define PIN_SPI_MISO     PIN_NC
#define PIN_SPI_CS       PIN_NC
#define PIN_SPI_HS       PIN_NC   // "datos listos" del S3 (entrada, opcional pero recomendado)
#define SPI_LINK_HZ      4000000

// ---- Canales LEDC (no cambiar salvo conflicto) ----
#define LEDC_CH_MOT_L    0
#define LEDC_CH_MOT_R    1
#define LEDC_CH_SERVO    2
#define LEDC_CH_RGB_R    3
#define LEDC_CH_RGB_G    4
#define LEDC_CH_RGB_B    5
